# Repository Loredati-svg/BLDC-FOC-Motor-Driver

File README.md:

# BLDC-FOC-Motor-Driver

Single-motor **BLDC / PMSM driver with sensored Field-Oriented Control (FOC)**.
It is the motor-control building block for a two-wheeled self-balancing robot, and it also works as a standalone driver on the bench, commanded and monitored over USB.

Rev A is a **test board**: the motor is screwed to the centre of the PCB, with the magnetic encoder sitting right under the motor shaft.

## Key specs

| | |
|---|---|
| Supply | 3S–6S LiPo, designed around **4S** (16.8 V max) |
| Target motor | BGM5208-75T gimbal motor (24N22P, 11 pole pairs, 15 Ω ph-ph, ~1.3 A max on 4S) |
| Control | Sensored FOC, center-aligned PWM at 20 kHz |
| Current sensing | 3-shunt low-side, 50 mΩ + DRV8323 CSA, gain ×10 → ±3.3 A full scale |
| Position feedback | MPS MA730 14-bit magnetic encoder (SPI), centred on the motor shaft |
| Interfaces | USB-C (CDC virtual COM: commands + telemetry), SWD via Tag-Connect TC2030 |
| Logic supply | DRV8323 integrated buck → 5 V → AP2112K LDO → 3.3 V; USB can power the logic for bench work |
| Protection | TVS on VBAT, gate-driver VDS overcurrent, UVLO, thermal shutdown, ESD + polyfuse on USB |

## Architecture

```
VBAT ─► TVS + bulk ─┬─► 3-phase inverter (6× 60 V MOSFET) ─► motor U V W
                    │          │
                    │      3× 50 mΩ low-side shunts ─► DRV8323 CSA ─► ADC (PA0–PA2)
                    │
                    └─► DRV8323RH ── buck ─► +5 V ─► LDO ─► +3V3
                             ▲
STM32G431 ── 6× PWM (TIM1) ──┘   ◄── MA730 encoder (SPI1) · VBAT sense · USB · SWD
```

## Main components

| Block | Part |
|---|---|
| MCU | STM32G431CBU6 (Cortex-M4F 170 MHz, CORDIC), 12 MHz crystal |
| Gate driver | TI DRV8323RH (hardware-strapped config, integrated 5 V buck) |
| Power stage | 6× TI CSD18540Q5B, 60 V, SON 5×6 |
| Current sensing | 3× 50 mΩ 4-terminal (Kelvin) shunts, DRV8323 internal amplifiers |
| Encoder | MPS MA730 + diametral magnet (Ø5 × 3 mm, ~1.5 mm air gap) |
| Supplies | DRV8323 buck (33 µH) → 5 V, AP2112K-3.3 LDO, ferrite-filtered VDDA/VREF+ |
| Protection | SMBJ26A TVS on VBAT, USBLC6-2SC6 ESD on USB, polyfuse + Schottky diode-OR on VBUS |
| Connectors | XT30 (battery), MR30 + solder pads (motor phases), USB-C, Tag-Connect TC2030 |

## Gate driver configuration (hardware straps)

| Pin | Setting | Value |
|---|---|---|
| MODE | tied to GND | 6x PWM |
| IDRIVE | 75 kΩ to GND | 60 mA source / 120 mA sink |
| VDS | tied to GND | 0.06 V trip (≈ 25–30 A with CSD18540Q5B) |
| GAIN | 47 kΩ to GND | ×10 |

Each strap has a spare DNP footprint to DVDD, so the setting can be changed on the bench.

## Current sense

```
V_SO       = VREF/2 + I × R_shunt × G = 1.65 V + I × 0.05 Ω × 10
Full scale = 1.65 V / (G × R_shunt)  = 1.65 V / (10 × 0.05 Ω) = ±3.3 A  (linear ≈ ±2.8 A)
P_shunt    = I² × R_shunt = (1.3 A)² × 0.05 Ω ≈ 85 mW
```

## MCU pinout

| Function | Pins |
|---|---|
| PWM (TIM1) | PA8 / PB13 (A), PA9 / PB14 (B), PA10 / PB15 (C) |
| Driver control | PB5 → EN, PB12 ← nFAULT |
| Phase currents | PA0, PA1, PA2 (ADC1, RC filtered) |
| Battery voltage | PA3 (VBAT / 11) |
| Encoder (SPI1) | PA4 CS, PA5 SCK, PA6 MISO, PA7 MOSI |
| USB | PA11 D−, PA12 D+ |
| Debug | PA13 SWDIO, PA14 SWCLK, PB3 SWO, PG10 NRST |
| LEDs | PC10 status, PC11 fault |

The full configuration is in the STM32CubeMX project (`.ioc`) in the `Firmware` folder.

## Repository structure

```
Firmware/   STM32CubeMX project and firmware
Hardware/   KiCad project (schematic, PCB)
```

## Libraries

This project uses the shared KiCad libraries from L2-Hardware.

1. Clone the library repository **in the same parent folder as your project folders**:

```bash
   git clone https://github.com/L2-Hardware/Kicad_Libs
```

   Expected folder structure:

```
   Kicad/
   ├── Kicad_Libs/
   ├── Project1/
   ├── Project2/
   └── ...
```

2. Inside the project folder, run `bring_libs.bat` to import the libraries into the project.

## Roadmap

- [x] Architecture and component selection
- [x] Schematic: connectors · power · gate driver · inverter · current sense · encoder · MCU
- [ ] ERC clean and footprint assignment
- [ ] PCB layout (4 layers)
- [ ] Fabrication and assembly
- [ ] Bring-up: power rails, SWD, encoder, PWM and dead-time, current-sense calibration
- [ ] Firmware: open loop → current loop → velocity / position loops
- [ ] Rev B: round board mounted on the back of the motor
- [ ] Integration in the self-balancing robot

## Author

Lorenzo Dati

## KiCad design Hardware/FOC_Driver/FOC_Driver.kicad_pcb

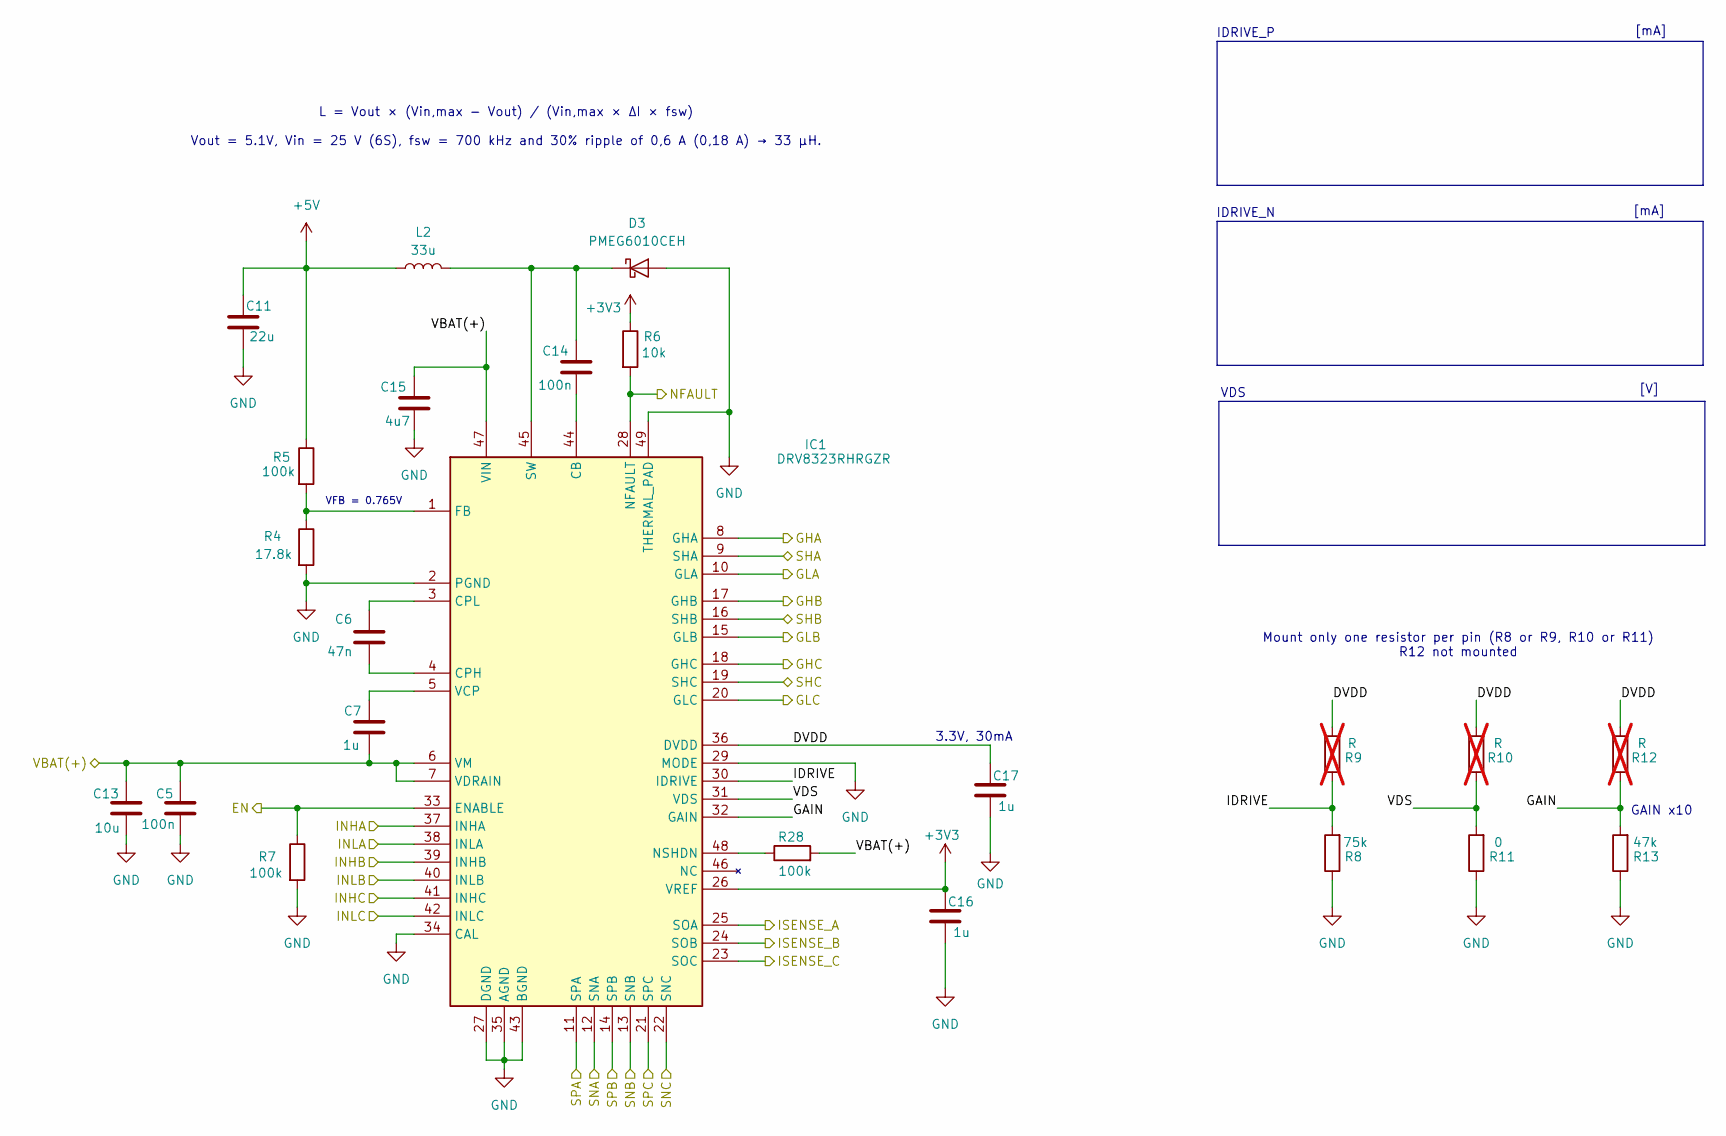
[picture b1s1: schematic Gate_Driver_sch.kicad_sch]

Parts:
C5: 100n; 0603
C6: 47n; 0603
C7: 1u; 0603
C11: 22u; 1206
C13: 10u; 1210
C14: 100n; 0402
C15: 4u7; 0805
C16, C17: 1u; 0402
D3: PMEG6010CEH; D_SOD-123F
IC1: DRV8323RHRGZR; QFN50P700X700X100-49N-D; Mouser Part Number 595-DRV8323RHRGZR
L2: 33u; L_Bourns_SRN6045TA
R4: 17.8k; 0402
R5, R7, R28: 100k; 0402
R6: 10k; 0402
R8: 75k; 0402
R9, R10, R12: R; 0402; not fitted
R11: 0; 0402
R13: 47k; 0402

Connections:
+3V3: C16.1, IC1.26 (VREF), R6.1; also elsewhere on the board
+5V: C11.1, L2.1, R5.1; also elsewhere on the board
/Gate_Driver/DVDD: C17.1, IC1.36 (DVDD), R9.2, R10.2, R12.2
/Gate_Driver/EN: IC1.33 (ENABLE), R7.1; also elsewhere on the board
/Gate_Driver/GAIN: IC1.32 (GAIN), R12.1, R13.2
/Gate_Driver/GHA: IC1.8 (GHA); also elsewhere on the board
/Gate_Driver/GHB: IC1.17 (GHB); also elsewhere on the board
/Gate_Driver/GHC: IC1.18 (GHC); also elsewhere on the board
/Gate_Driver/GLA: IC1.10 (GLA); also elsewhere on the board
/Gate_Driver/GLB: IC1.15 (GLB); also elsewhere on the board
/Gate_Driver/GLC: IC1.20 (GLC); also elsewhere on the board
/Gate_Driver/IDRIVE: IC1.30 (IDRIVE), R8.2, R9.1
/Gate_Driver/INHA: IC1.37 (INHA); also elsewhere on the board
/Gate_Driver/INHB: IC1.39 (INHB); also elsewhere on the board
/Gate_Driver/INHC: IC1.41 (INHC); also elsewhere on the board
/Gate_Driver/INLA: IC1.38 (INLA); also elsewhere on the board
/Gate_Driver/INLB: IC1.40 (INLB); also elsewhere on the board
/Gate_Driver/INLC: IC1.42 (INLC); also elsewhere on the board
/Gate_Driver/ISENSE_A: IC1.25 (SOA); also elsewhere on the board
/Gate_Driver/ISENSE_B: IC1.24 (SOB); also elsewhere on the board
/Gate_Driver/ISENSE_C: IC1.23 (SOC); also elsewhere on the board
/Gate_Driver/NFAULT: IC1.28 (NFAULT), R6.2; also elsewhere on the board
/Gate_Driver/SNA: IC1.12 (SNA); also elsewhere on the board
/Gate_Driver/SNB: IC1.13 (SNB); also elsewhere on the board
/Gate_Driver/SNC: IC1.22 (SNC); also elsewhere on the board
/Gate_Driver/SPA: IC1.11 (SPA); also elsewhere on the board
/Gate_Driver/SPB: IC1.14 (SPB); also elsewhere on the board
/Gate_Driver/SPC: IC1.21 (SPC); also elsewhere on the board
/Gate_Driver/VBAT(+): C5.1, C7.1, C13.1, C15.2, IC1.6 (VM), IC1.7 (VDRAIN), IC1.47 (VIN), R28.2; also elsewhere on the board
/Gate_Driver/VDS: IC1.31 (VDS), R10.1, R11.2
/SHA: IC1.9 (SHA); also elsewhere on the board
/SHB: IC1.16 (SHB); also elsewhere on the board
/SHC: IC1.19 (SHC); also elsewhere on the board
GND: C5.2, C11.2, C13.2, C15.1, C16.2, C17.2, D3.2 (A), IC1.2 (PGND), IC1.27 (DGND), IC1.29 (MODE), IC1.34 (CAL), IC1.35 (AGND), IC1.43 (BGND), IC1.49 (THERMAL_PAD), R4.2, R7.2, R8.1, R11.1, R13.1; also elsewhere on the board
unnamed: C14.2, D3.1 (K), IC1.45 (SW), L2.2
unnamed: C14.1, IC1.44 (CB)
unnamed: C6.1, IC1.4 (CPH)
unnamed: C6.2, IC1.3 (CPL)
unnamed: IC1.1 (FB), R4.1, R5.2
unnamed: IC1.48 (NSHDN), R28.1
unnamed: C7.2, IC1.5 (VCP)

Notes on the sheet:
[V]
3.3V, 30mA
VDS
[mA]
VFB = 0.765V
GAIN x10
IDRIVE_P
Mount only one resistor per pin (R8 or R9, R10 or R11) R12 not mounted
IDRIVE_N
L = Vout × (Vin,max − Vout) / (Vin,max × ΔI × fsw) Vout = 5.1V, Vin = 25 V (6S), fsw = 700 kHz and 30% ripple of 0,6 A (0,18 A) → 33 µH.

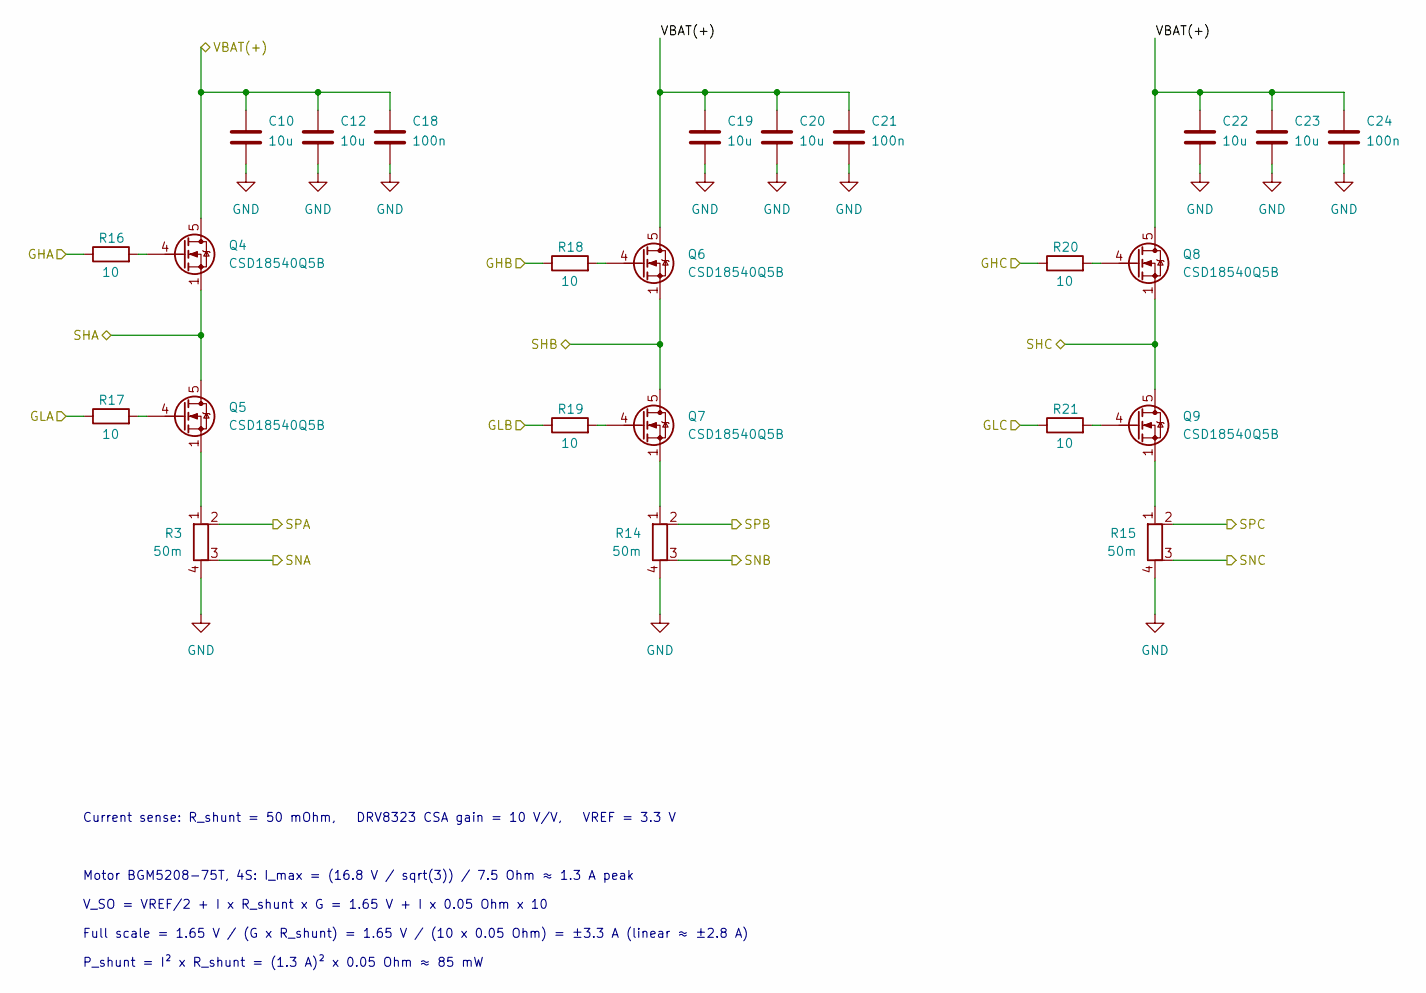
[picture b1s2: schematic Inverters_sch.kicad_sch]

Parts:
C10, C12, C19, C20, C22, C23: 10u; C_1206_3216Metric
C18, C21, C24: 100n; C_0603_1608Metric
Q4, Q5, Q6, Q7, Q8, Q9: CSD18540Q5B; TDSON-8-1
R3, R14, R15: 50m; R_Shunt_Vishay_WSK2512_6332Metric_T1.19mm
R16, R17, R18, R19, R20, R21: 10; R_0603_1608Metric

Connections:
/Gate_Driver/GHA: R16.1; also elsewhere on the board
/Gate_Driver/GHB: R18.1; also elsewhere on the board
/Gate_Driver/GHC: R20.1; also elsewhere on the board
/Gate_Driver/GLA: R17.1; also elsewhere on the board
/Gate_Driver/GLB: R19.1; also elsewhere on the board
/Gate_Driver/GLC: R21.1; also elsewhere on the board
/Gate_Driver/SNA: R3.3; also elsewhere on the board
/Gate_Driver/SNB: R14.3; also elsewhere on the board
/Gate_Driver/SNC: R15.3; also elsewhere on the board
/Gate_Driver/SPA: R3.2; also elsewhere on the board
/Gate_Driver/SPB: R14.2; also elsewhere on the board
/Gate_Driver/SPC: R15.2; also elsewhere on the board
/Gate_Driver/VBAT(+): C10.1, C12.1, C18.1, C19.1, C20.1, C21.1, C22.1, C23.1, C24.1, Q4.5 (D), Q6.5 (D), Q8.5 (D); also elsewhere on the board
/SHA: Q4.1 (S), Q4.2 (S), Q4.3 (S), Q5.5 (D); also elsewhere on the board
/SHB: Q6.1 (S), Q6.2 (S), Q6.3 (S), Q7.5 (D); also elsewhere on the board
/SHC: Q8.1 (S), Q8.2 (S), Q8.3 (S), Q9.5 (D); also elsewhere on the board
GND: C10.2, C12.2, C18.2, C19.2, C20.2, C21.2, C22.2, C23.2, C24.2, R3.4, R14.4, R15.4; also elsewhere on the board
unnamed: Q4.4 (G), R16.2
unnamed: Q5.4 (G), R17.2
unnamed: Q5.1 (S), Q5.2 (S), Q5.3 (S), R3.1
unnamed: Q6.4 (G), R18.2
unnamed: Q7.4 (G), R19.2
unnamed: Q7.1 (S), Q7.2 (S), Q7.3 (S), R14.1
unnamed: Q8.4 (G), R20.2
unnamed: Q9.4 (G), R21.2
unnamed: Q9.1 (S), Q9.2 (S), Q9.3 (S), R15.1

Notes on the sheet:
Current sense: R_shunt = 50 mOhm, DRV8323 CSA gain = 10 V/V, VREF = 3.3 V Motor BGM5208-75T, 4S: I_max = (16.8 V / sqrt(3)) / 7.5 Ohm ≈ 1.3 A peak V_SO = VREF/2 + I x R_shunt x G = 1.65 V + I x 0.05 Ohm x 10 Full scale = 1.65 V / (G x R_shunt) = 1.65 V / (10 x 0.05 Ohm) = ±3.3 A (linear ≈ ±2.8 A) P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

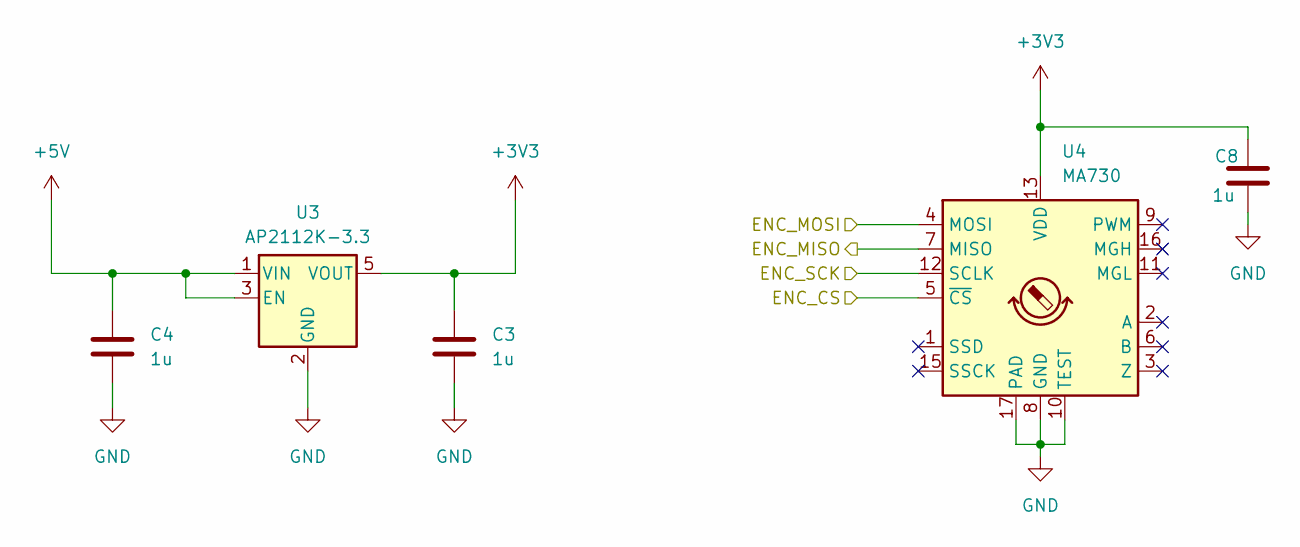
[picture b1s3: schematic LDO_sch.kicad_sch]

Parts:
C3, C4, C8: 1u; C_0402_1005Metric
U3: AP2112K-3.3; SOT-23-5
U4: MA730; QFN-16-1EP_3x3mm_P0.5mm_EP1.75x1.75mm

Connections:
+3V3: C3.1, C8.1, U3.5 (VOUT), U4.13 (VDD); also elsewhere on the board
+5V: C4.1, U3.1 (VIN), U3.3 (EN); also elsewhere on the board
/LDO + Encoder/ENC_CS: U4.5 (~CS); also elsewhere on the board
/LDO + Encoder/ENC_MISO: U4.7 (MISO); also elsewhere on the board
/LDO + Encoder/ENC_MOSI: U4.4 (MOSI); also elsewhere on the board
/LDO + Encoder/ENC_SCK: U4.12 (SCLK); also elsewhere on the board
GND: C3.2, C4.2, C8.2, U3.2 (GND), U4.8 (GND), U4.10 (TEST), U4.17 (PAD); also elsewhere on the board

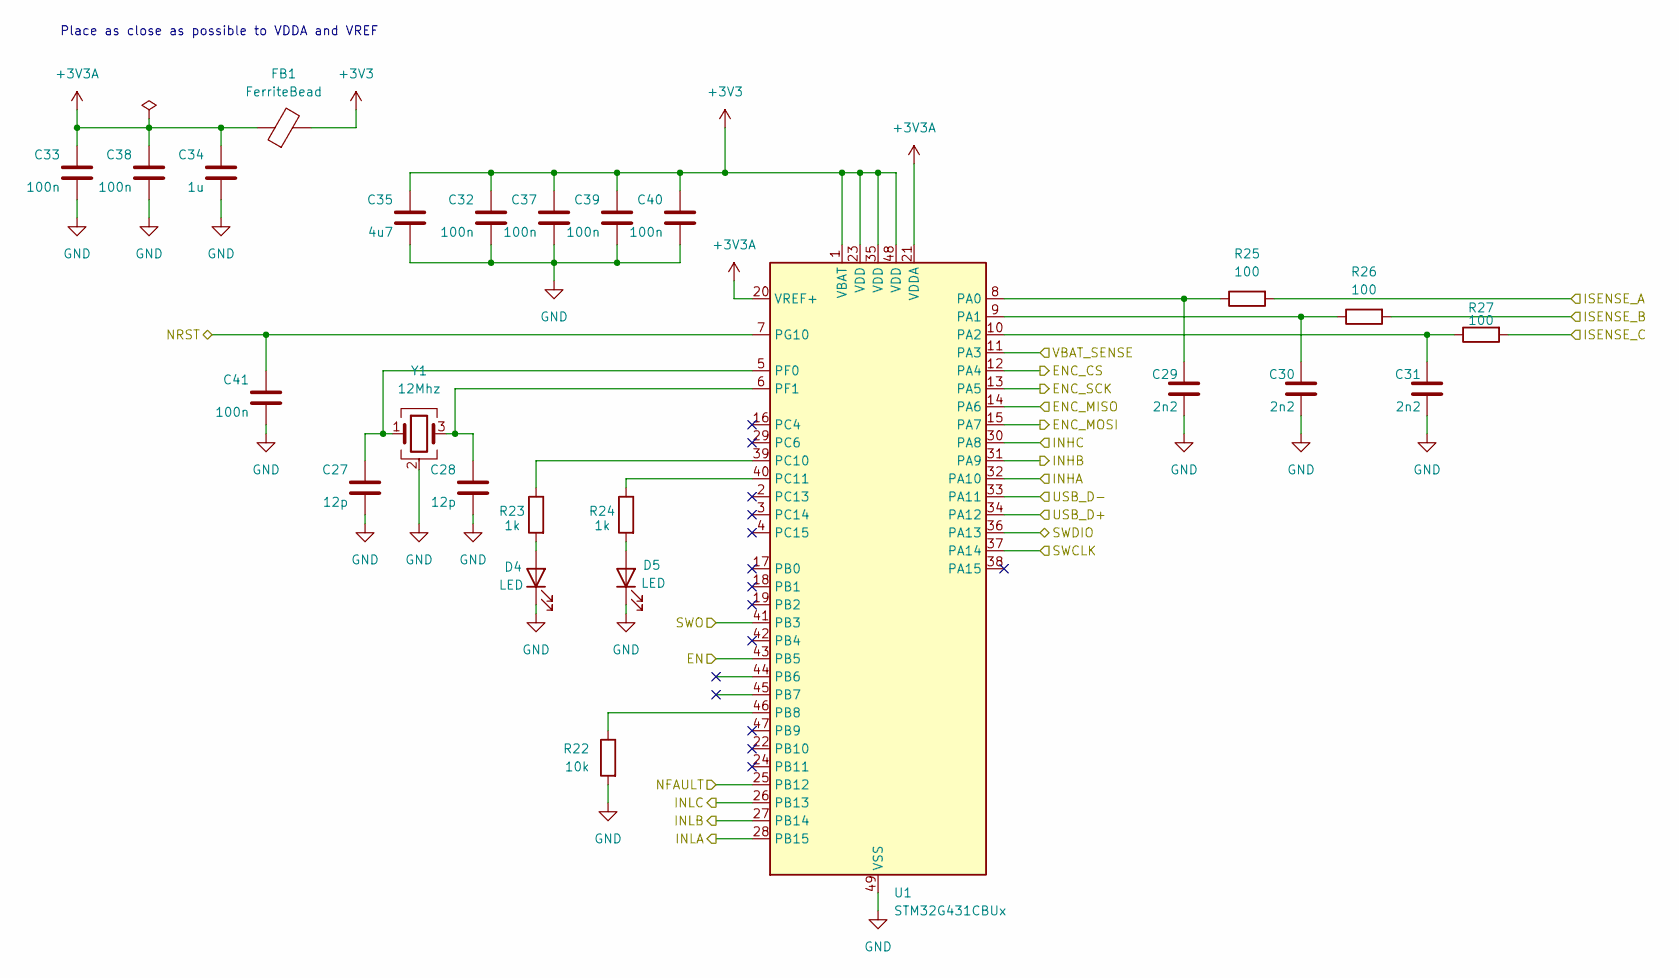
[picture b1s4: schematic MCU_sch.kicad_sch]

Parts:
C27, C28: 12p; 0402
C29, C30, C31: 2n2; 0402
C32, C33, C37, C38, C39, C40, C41: 100n; 0402
C34: 1u; 0603
C35: 4u7; 0805
D4, D5: LED; 0603_pol
FB1: FerriteBead; 0603
R22: 10k; 0402
R23, R24: 1k; 0402
R25, R26, R27: 100; 0402
U1: STM32G431CBUx; QFN-48-1EP_7x7mm_P0.5mm_EP5.6x5.6mm
Y1: 12Mhz; Crystal_SMD_ECX-32_Series_4Pin_3.2x2.5mm

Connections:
+3V3: C32.2, C35.2, C37.2, C39.2, C40.2, FB1.2, U1.1 (VBAT), U1.23 (VDD), U1.35 (VDD), U1.48 (VDD); also elsewhere on the board
+3V3A: C33.2, C34.2, C38.2, FB1.1, U1.20 (VREF+), U1.21 (VDDA)
/Connectors/NRST: C41.2, U1.7 (PG10); also elsewhere on the board
/Connectors/SWCLK: U1.37 (PA14); also elsewhere on the board
/Connectors/SWDIO: U1.36 (PA13); also elsewhere on the board
/Connectors/SWO: U1.41 (PB3); also elsewhere on the board
/Connectors/USB_D+: U1.34 (PA12); also elsewhere on the board
/Connectors/USB_D-: U1.33 (PA11); also elsewhere on the board
/Connectors/VBAT_SENSE: U1.11 (PA3); also elsewhere on the board
/Gate_Driver/EN: U1.43 (PB5); also elsewhere on the board
/Gate_Driver/INHA: U1.32 (PA10); also elsewhere on the board
/Gate_Driver/INHB: U1.31 (PA9); also elsewhere on the board
/Gate_Driver/INHC: U1.30 (PA8); also elsewhere on the board
/Gate_Driver/INLA: U1.28 (PB15); also elsewhere on the board
/Gate_Driver/INLB: U1.27 (PB14); also elsewhere on the board
/Gate_Driver/INLC: U1.26 (PB13); also elsewhere on the board
/Gate_Driver/ISENSE_A: R25.2; also elsewhere on the board
/Gate_Driver/ISENSE_B: R26.2; also elsewhere on the board
/Gate_Driver/ISENSE_C: R27.2; also elsewhere on the board
/Gate_Driver/NFAULT: U1.25 (PB12); also elsewhere on the board
/LDO + Encoder/ENC_CS: U1.12 (PA4); also elsewhere on the board
/LDO + Encoder/ENC_MISO: U1.14 (PA6); also elsewhere on the board
/LDO + Encoder/ENC_MOSI: U1.15 (PA7); also elsewhere on the board
/LDO + Encoder/ENC_SCK: U1.13 (PA5); also elsewhere on the board
GND: C27.1, C28.1, C29.1, C30.1, C31.1, C32.1, C33.1, C34.1, C35.1, C37.1, C38.1, C39.1, C40.1, C41.1, D4.1 (K), D5.1 (K), R22.2, U1.49 (VSS), Y1.2 (G), Y1.4 (G); also elsewhere on the board
unnamed: D4.2 (A), R23.2
unnamed: D5.2 (A), R24.2
unnamed: C29.2, R25.1, U1.8 (PA0)
unnamed: C30.2, R26.1, U1.9 (PA1)
unnamed: C31.2, R27.1, U1.10 (PA2)
unnamed: R22.1, U1.46 (PB8)
unnamed: R23.1, U1.39 (PC10)
unnamed: R24.1, U1.40 (PC11)
unnamed: C27.2, U1.5 (PF0), Y1.1
unnamed: C28.2, U1.6 (PF1), Y1.3

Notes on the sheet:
Place as close as possible to VDDA and VREF

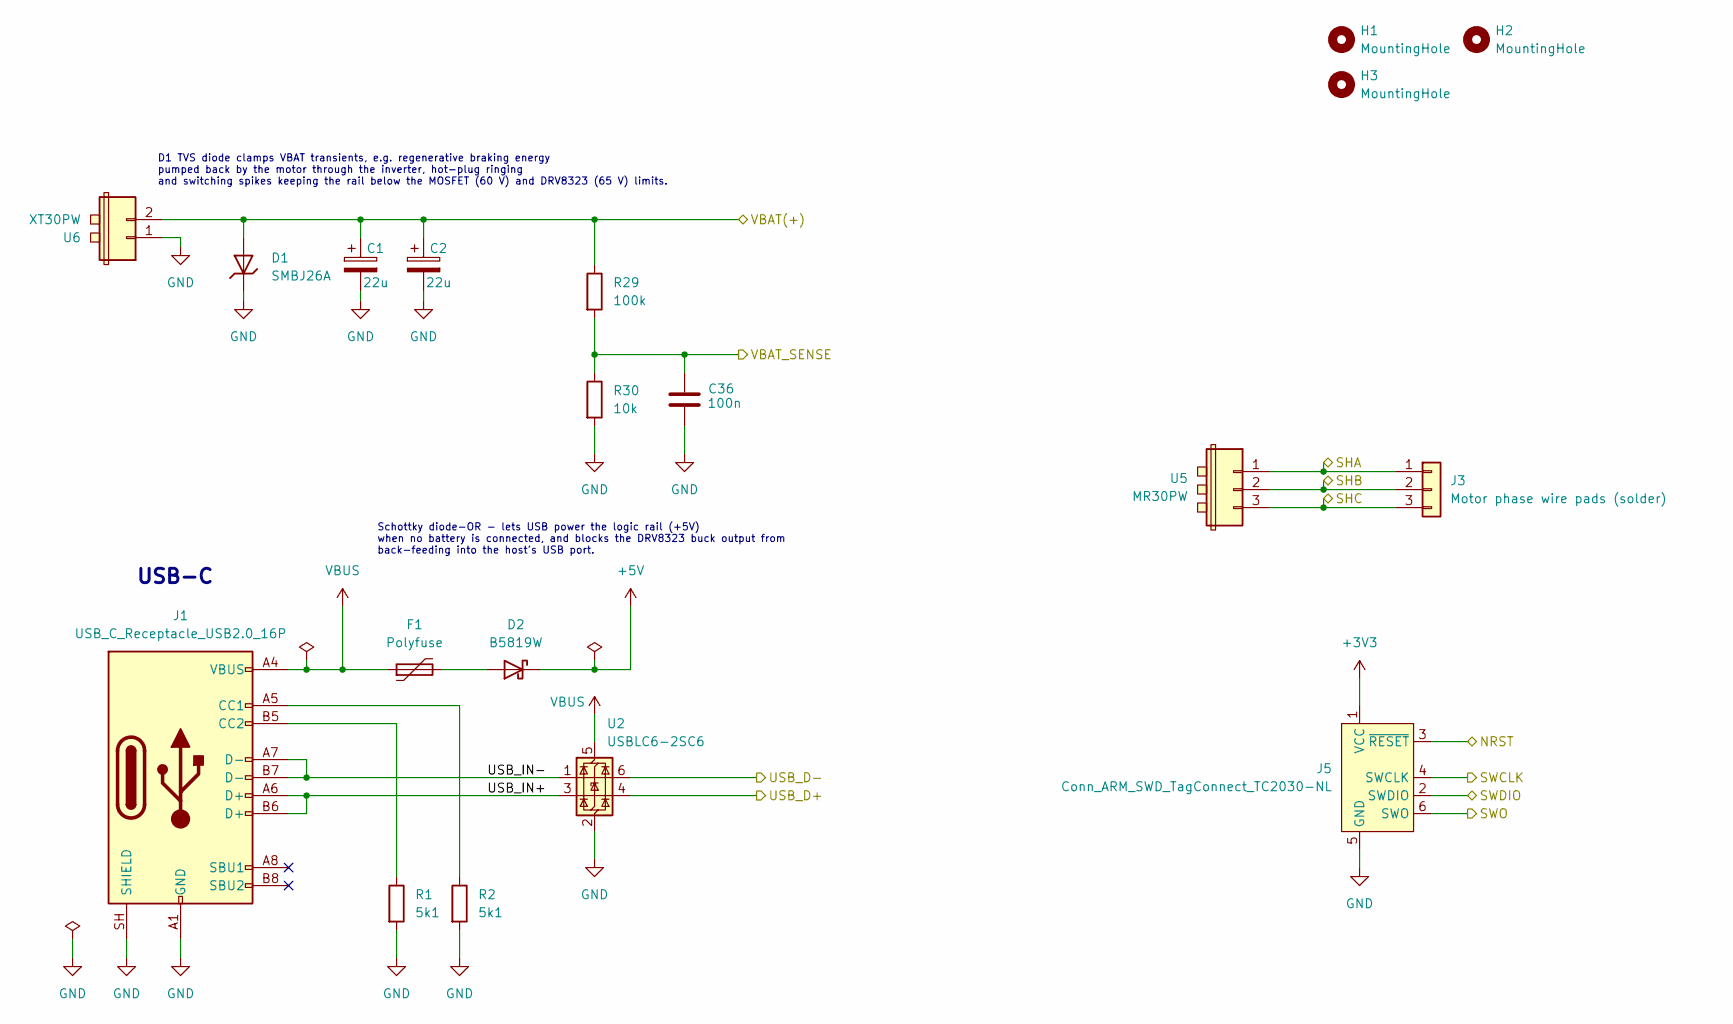
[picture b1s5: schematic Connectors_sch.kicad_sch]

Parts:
C1, C2: 22u; CP_Elec_6.3x5.4
C36: 100n; 0402
D1: SMBJ26A; D_SMB; Part SMBJ26A; LCSC C19077580
D2: B5819W; D_SOD-123; Forward Voltage (Vf@If) 900mV@3A; Reverse Voltage (Vr) 40V; Part B5819W; LCSC C64885
F1: Polyfuse; Fuse_1206_3216Metric
H1, H2, H3: MountingHole; MountingHole_2.7mm_M2.5_DIN965_Pad_TopOnly
J1: USB_C_Receptacle_USB2.0_16P; USB_C_Receptacle_GCT_USB4105-xx-A_16P_TopMnt_Horizontal
J3: Motor phase wire pads (solder); SolderWire-0.5sqmm_1x03_P4.6mm_D0.9mm_OD2.1mm
J5: Conn_ARM_SWD_TagConnect_TC2030-NL; Tag-Connect_TC2030-IDC-NL_2x03_P1.27mm_Vertical
R1, R2: 5k1; R_0402_1005Metric
R29: 100k; 0603
R30: 10k; 0603
U2: USBLC6-2SC6; SOT-23-6
U5: MR30PW; AMASS_MR30PW-M_1x03_P3.50mm_Horizontal
U6: XT30PW; AMASS_XT30PW-M_1x02_P2.50mm_Horizontal

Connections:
+3V3: J5.1 (VCC); also elsewhere on the board
+5V: D2.1; also elsewhere on the board
/Connectors/NRST: J5.3 (~RESET); also elsewhere on the board
/Connectors/SWCLK: J5.4 (SWCLK); also elsewhere on the board
/Connectors/SWDIO: J5.2 (SWDIO); also elsewhere on the board
/Connectors/SWO: J5.6 (SWO); also elsewhere on the board
/Connectors/USB_D+: U2.4 (I/O2); also elsewhere on the board
/Connectors/USB_D-: U2.6 (I/O1); also elsewhere on the board
/Connectors/USB_IN+: J1.A6 (D+), J1.B6 (D+), U2.3 (I/O2)
/Connectors/USB_IN-: J1.A7 (D-), J1.B7 (D-), U2.1 (I/O1)
/Connectors/VBAT_SENSE: C36.2, R29.2, R30.1; also elsewhere on the board
/Gate_Driver/VBAT(+): C1.1, C2.1, D1.2, R29.1, U6.2; also elsewhere on the board
/SHA: J3.1, U5.1; also elsewhere on the board
/SHB: J3.2, U5.2; also elsewhere on the board
/SHC: J3.3, U5.3; also elsewhere on the board
GND: C1.2, C2.2, C36.1, D1.1, J1.A1 (GND), J1.A12 (GND), J1.B1 (GND), J1.B12 (GND), J1.SH (SHIELD), J5.5 (GND), R1.2, R2.2, R30.2, U2.2 (GND), U6.1; also elsewhere on the board
unnamed: D2.2, F1.2
unnamed: J1.A5 (CC1), R2.1
unnamed: J1.B5 (CC2), R1.1
VBUS: F1.1, J1.A4 (VBUS), J1.A9 (VBUS), J1.B4 (VBUS), J1.B9 (VBUS), U2.5 (VBUS)

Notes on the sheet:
Schottky diode-OR - lets USB power the logic rail (+5V) when no battery is connected, and blocks the DRV8323 buck output from back-feeding into the host's USB port.
D1 TVS diode clamps VBAT transients, e.g. regenerative braking energy pumped back by the motor through the inverter, hot-plug ringing and switching spikes keeping the rail below the MOSFET (60 V) and DRV8323 (65 V) limits.
USB-C

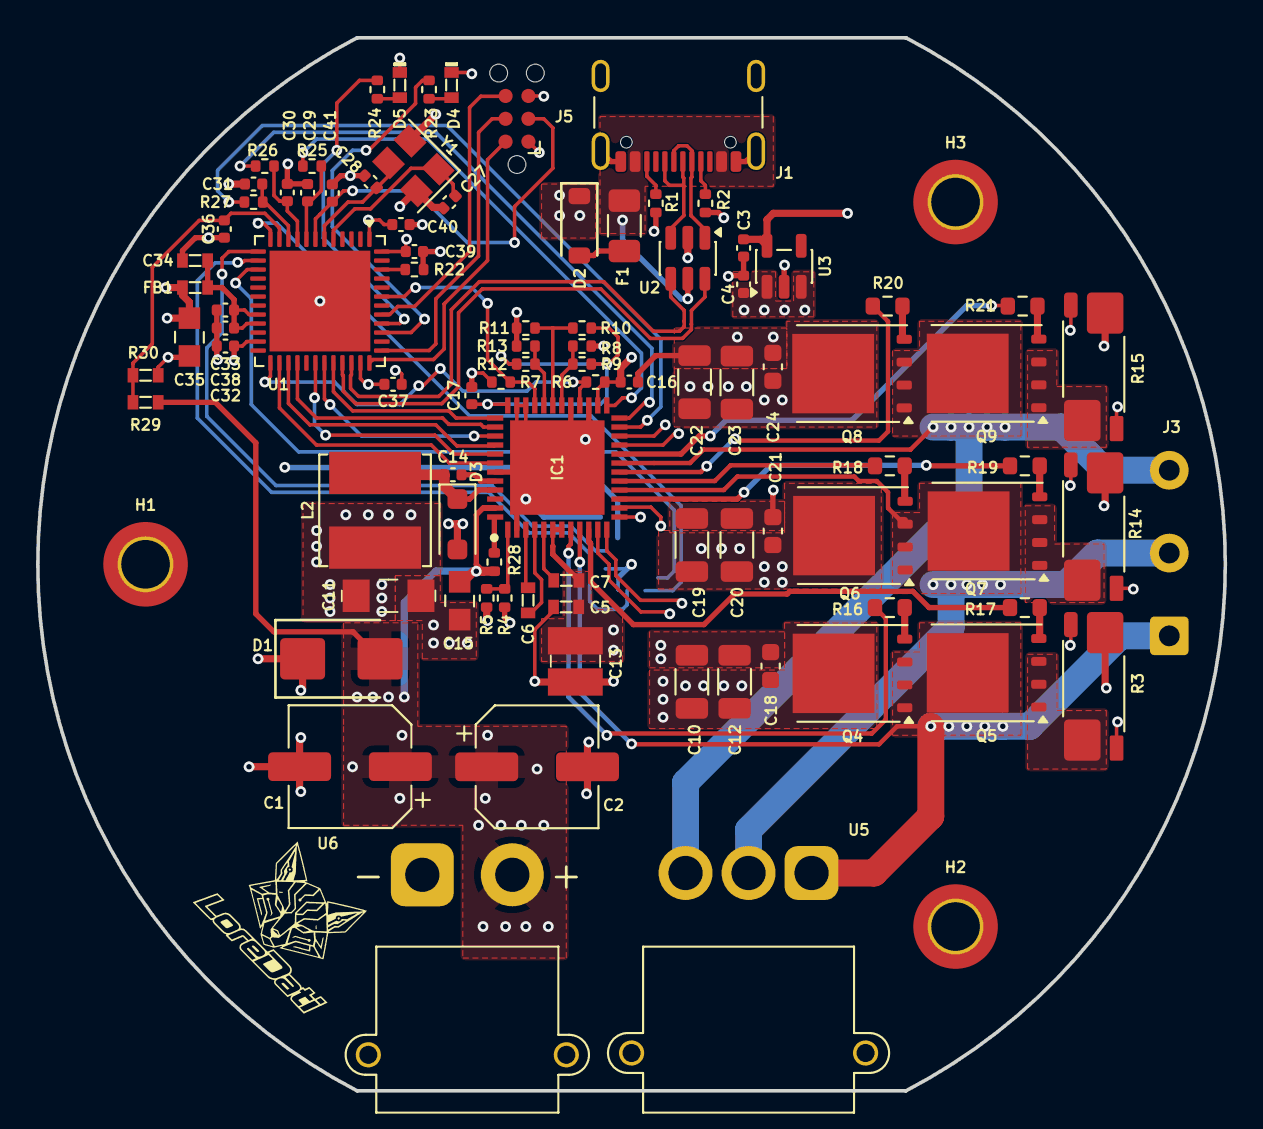
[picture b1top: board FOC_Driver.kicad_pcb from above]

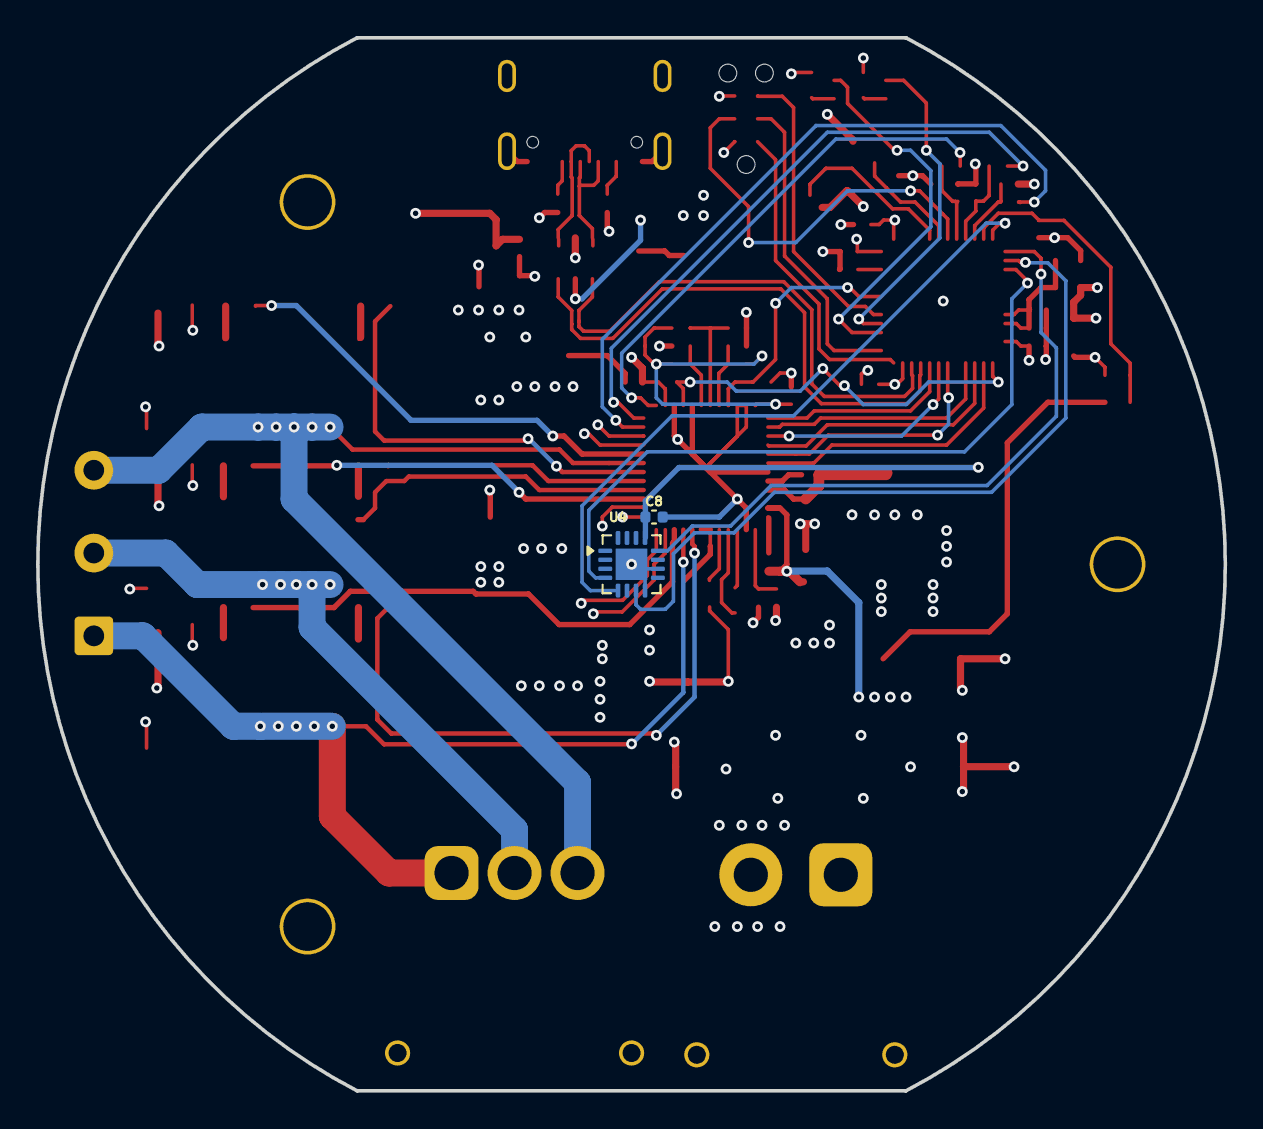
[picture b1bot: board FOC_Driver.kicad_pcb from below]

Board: 4 copper layers, 66.0 x 58.5 mm, 96 parts (2 on the bottom side), 78 nets.

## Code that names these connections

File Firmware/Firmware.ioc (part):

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Mcu.Name=STM32G431C(6-8-B)Ux
Mcu.Package=UFQFPN48
Mcu.UserName=STM32G431CBUx
PA0.GPIOParameters=GPIO_Label
PA0.GPIO_Label=ISENSE_A
PA0.Mode=IN1-Single-Ended
PA0.Signal=ADC1_IN1
PA1.GPIOParameters=GPIO_Label
PA1.GPIO_Label=ISENSE_B
PA1.Mode=IN2-Single-Ended
PA1.Signal=ADC1_IN2
PA10.GPIOParameters=GPIO_Label
PA10.GPIO_Label=INHC
PA10.Signal=S_TIM1_CH3
PA11.Mode=Device
PA11.Signal=USB_DM
PA12.Mode=Device
PA12.Signal=USB_DP
PA13.Mode=Trace_Asynchronous_SW
PA13.Signal=SYS_JTMS-SWDIO
PA14.Mode=Trace_Asynchronous_SW
PA14.Signal=SYS_JTCK-SWCLK
PA2.GPIOParameters=GPIO_Label
PA2.GPIO_Label=ISENSE_C
PA2.Mode=IN3-Single-Ended
PA2.Signal=ADC1_IN3
PA3.Mode=IN4-Single-Ended
PA3.Signal=ADC1_IN4
PA4.GPIOParameters=GPIO_Label
PA4.GPIO_Label=ENC_CS
PA4.Signal=GPIO_Output
PA5.Mode=Full_Duplex_Master
PA5.Signal=SPI1_SCK
PA6.Mode=Full_Duplex_Master
PA6.Signal=SPI1_MISO
PA7.Mode=Full_Duplex_Master
PA7.Signal=SPI1_MOSI
PA8.GPIOParameters=GPIO_Label
PA8.GPIO_Label=INHA
PA8.Signal=S_TIM1_CH1
PA9.GPIOParameters=GPIO_Label
PA9.GPIO_Label=INHB
PA9.Signal=S_TIM1_CH2
PB12.GPIOParameters=GPIO_Label
PB12.GPIO_Label=NFAULT
PB12.Signal=GPIO_Input
PB13.GPIOParameters=GPIO_Label
PB13.GPIO_Label=INLA
PB13.Mode=PWM Generation1 CH1 CH1N
PB13.Signal=TIM1_CH1N
PB14.GPIOParameters=GPIO_Label
PB14.GPIO_Label=INLB
PB14.Mode=PWM Generation2 CH2 CH2N
PB14.Signal=TIM1_CH2N
PB15.GPIOParameters=GPIO_Label
PB15.GPIO_Label=INLC
PB15.Mode=PWM Generation3 CH3 CH3N
PB15.Signal=TIM1_CH3N
PB3.Mode=Trace_Asynchronous_SW
PB3.Signal=SYS_JTDO-SWO
PB5.GPIOParameters=GPIO_Label
PB5.GPIO_Label=EN
PB5.Signal=GPIO_Output
PB6.Mode=Asynchronous
PB6.Signal=USART1_TX
PB7.Mode=Asynchronous
PB7.Signal=USART1_RX
PC10.GPIOParameters=GPIO_Label
PC10.GPIO_Label=LED_STATUS
PC10.Signal=GPIO_Output
PC11.GPIOParameters=GPIO_Label
PC11.GPIO_Label=LED_FAULT
PC11.Signal=GPIO_Output
PF0-OSC_IN.Mode=HSE-External-Oscillator
PF0-OSC_IN.Signal=RCC_OSC_IN
PF1-OSC_OUT.Mode=HSE-External-Oscillator
PF1-OSC_OUT.Signal=RCC_OSC_OUT
RCC.HSE_VALUE=8000000
RCC.SYSCLKFreq_VALUE=170000000
RCC.SYSCLKSource=RCC_SYSCLKSOURCE_PLLCLK
board=custom
